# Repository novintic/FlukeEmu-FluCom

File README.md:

# FlukeEmu-FluCom
A HW/SW solution for Fluke 9010 mainframe emulation

The Idea is to use a Raspberry Pi to run a Fluke 9010a emulator in software and interface with the hardware (pods) by means
of an add on board/hat (basically to shift the levels and provide power to the pod). So far we have progressed from a proof
of concept to a pretty solid and stable emulation.

The advantages of using an approach like this are many, amongst them:
* cheap Fluke 9010a mainframe replacement using modern technology and thereby adding stuff like network capability, wireless LAN, remote access/VNC, bluetooth etc ‚for free‘
* the interface board can supply all the power rails to the pod so only one 12V wall adapter is needed to power the RaspberryPi and the pods
* the whole setup is portable and compact, you could in theory put the whole thing inside your cabinet/UUT and comfortably use VNC to remote control the Fluke. You could also run the thing ‚headless‘ making it even smaller.

For further instruction on the fluCom board, please check: FlukeEmu-FluCom/fluCom/readme.md

For further instruction on the flukeEmuWx software, please check: FlukeEmu-FluCom/flukeEmuWx/readme.md

## Credits
We would like to credit Adam Courchesne (@onecircuit) for coming up with the idea of a Fluke emulator and hardware combination
and of course for being the first one to actually write one and make it available.

## See also
https://forums.arcade-museum.com/threads/flukeemu-flucom-fluke-9010a-microsystem-troubleshooter-emulator.503305/

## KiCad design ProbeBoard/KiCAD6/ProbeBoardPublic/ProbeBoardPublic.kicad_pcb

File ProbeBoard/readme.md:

# Probe add-on- board for FluCom Raspberry Pi HAT

This add-on board for the FluCom Raspberry Pi HAT provides full probe functionality for the FlukeEmu/FluCom hardware/software Emulation of the Fluke 9010A Micro-System Troubleshooter.

Basically this makes the Fluke 9010A emulation feature- complete.

As much of the original circuitry as possible was implemented using a Raspberry PICO microcontroller. 

However, due to the original design of the probe, a significant amount of analog circuitry had to be reproduced in order to keep the system working with legacy probes.

The board and its design files are made available under the CERN Open Hardware License: https://ohwr.org/project/cernohl/wikis/Documents/CERN-OHL-version-2

Novitntic 11/2022

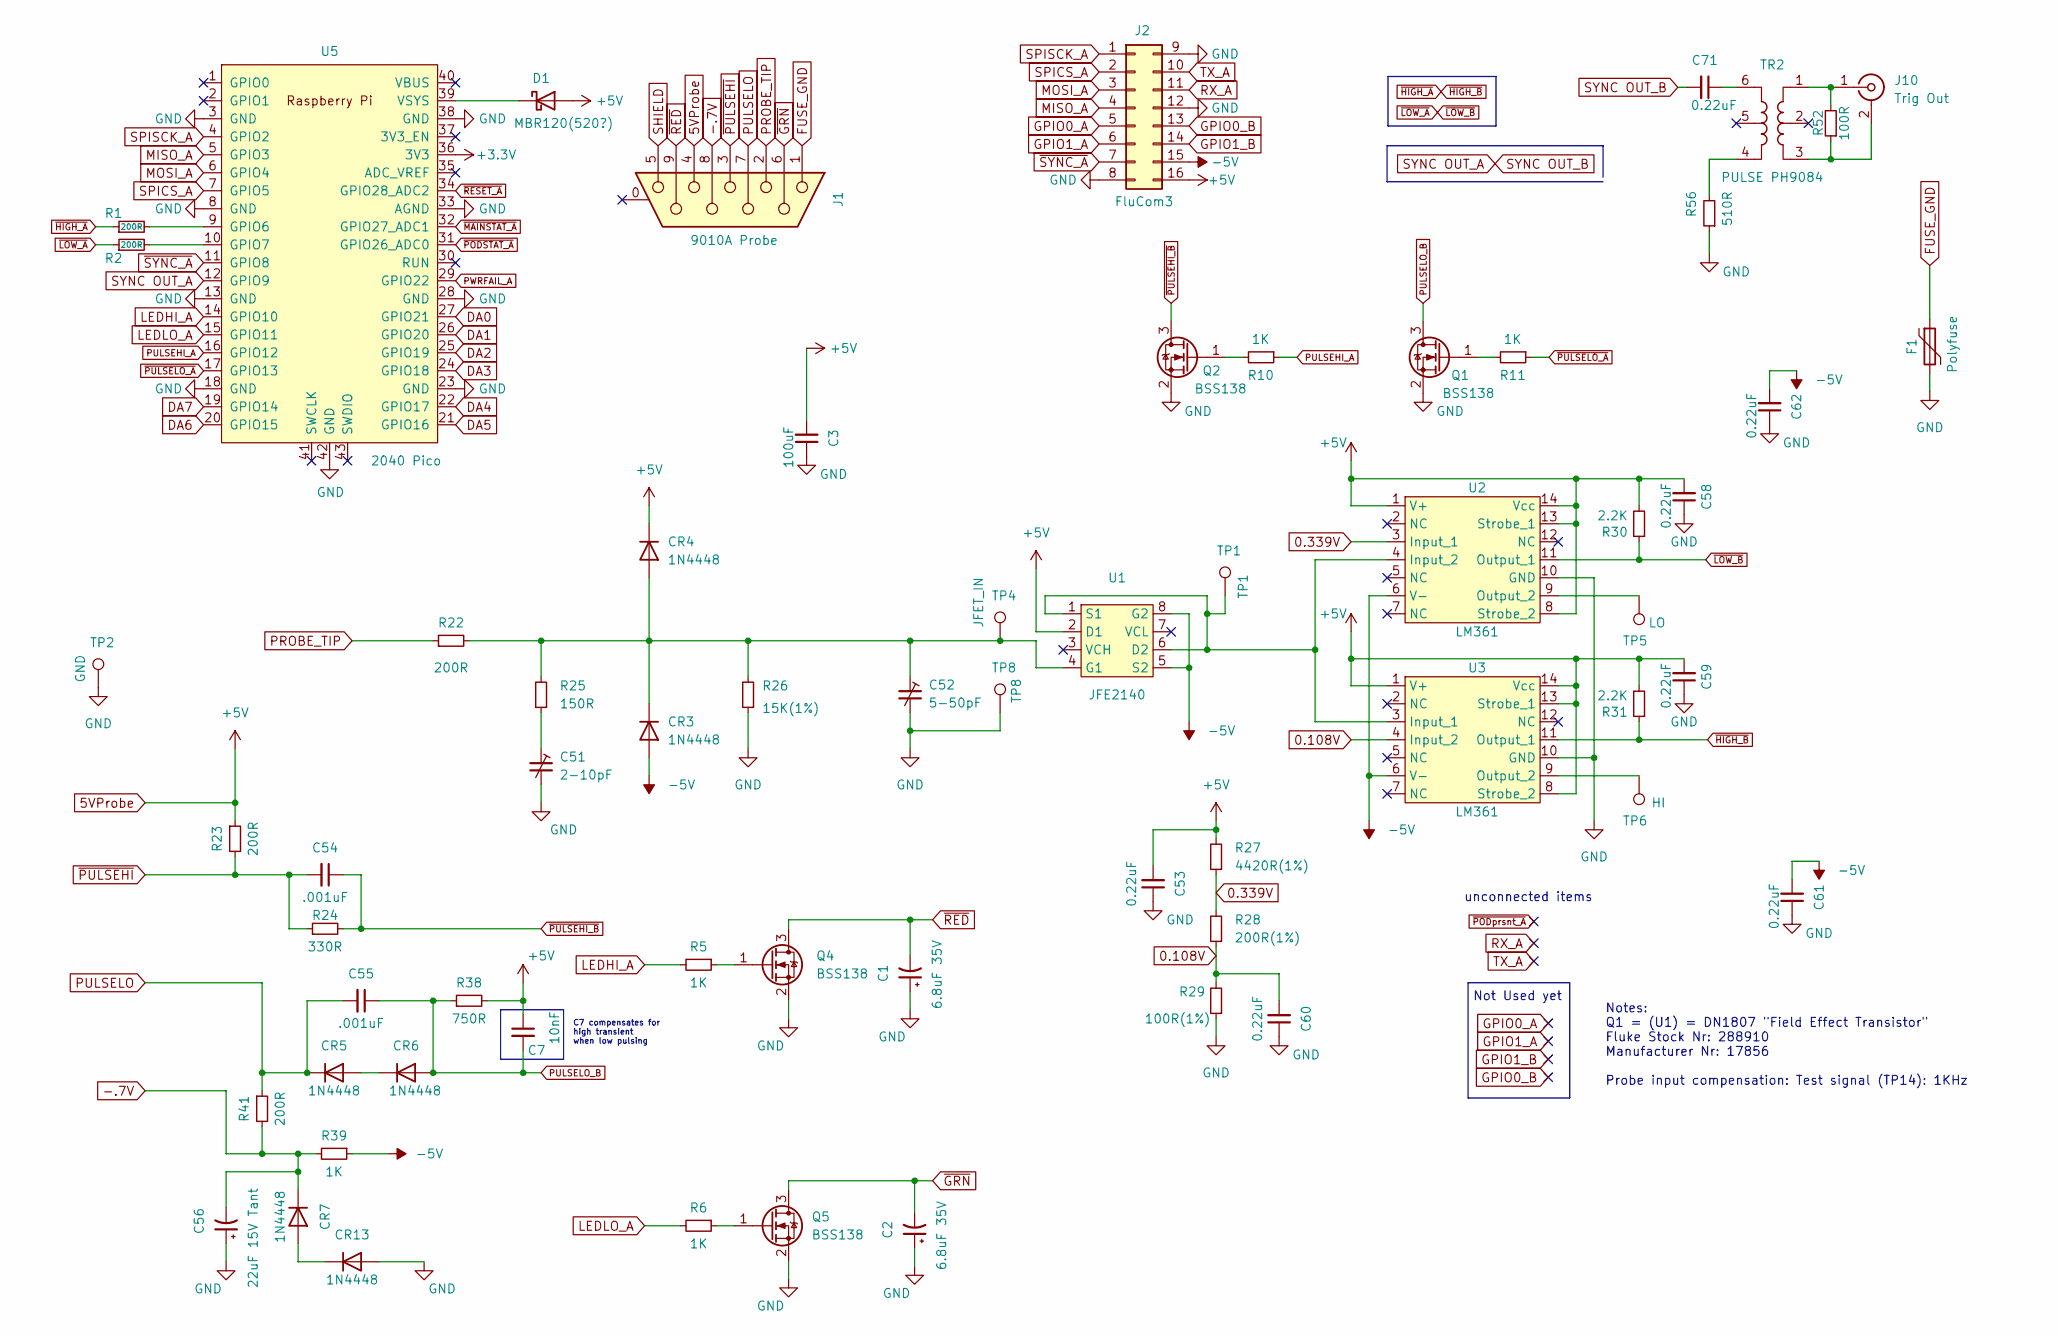
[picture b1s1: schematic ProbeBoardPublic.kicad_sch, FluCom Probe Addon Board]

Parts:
C1, C2: 6.8uF 35V; C_0805_2012Metric_Pad1.18x1.45mm_HandSolder
C3: 100uF; CP_Radial_D5.0mm_P2.50mm
C7: 10nF; C_0805_2012Metric_Pad1.18x1.45mm_HandSolder
C51: 2-10pF; C_1210_3225Metric
C52: 5-50pF; C_1210_3225Metric
C53, C58, C59, C60, C61, C62, C71: 0.22uF; C_0805_2012Metric_Pad1.18x1.45mm_HandSolder
C54, C55: .001uF; C_0805_2012Metric_Pad1.18x1.45mm_HandSolder
C56: 22uF 15V Tant; C_0805_2012Metric_Pad1.18x1.45mm_HandSolder
CR3, CR4, CR5, CR6, CR7, CR13: 1N4448; Nexperia_CFP3_SOD-123W
D1: MBR120(520?); Nexperia_CFP3_SOD-123W
F1: Polyfuse; C_1206_3216Metric_Pad1.33x1.80mm_HandSolder
J1: 9010A Probe; DSUB-9_Female_Horizontal_P2.77x2.84mm_EdgePinOffset4.94mm_H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
J2: FluCom3; PinHeader_2x08_P2.54mm_Vertical
J10: Trig Out; BNC_TEConnectivity_1478035_Horizontal
Q1, Q2, Q4, Q5: BSS138; SOT-23
R1, R2, R22, R23, R41: 200R; R_0805_2012Metric_Pad1.20x1.40mm_HandSolder
R5, R6, R10, R11, R39: 1K; R_0805_2012Metric_Pad1.20x1.40mm_HandSolder
R24: 330R; R_0805_2012Metric_Pad1.20x1.40mm_HandSolder
R25: 150R; R_0805_2012Metric_Pad1.20x1.40mm_HandSolder
R26: 15K(1%); R_0805_2012Metric_Pad1.20x1.40mm_HandSolder
R27: 4420R(1%); R_0805_2012Metric_Pad1.20x1.40mm_HandSolder
R28: 200R(1%); R_0805_2012Metric_Pad1.20x1.40mm_HandSolder
R29: 100R(1%); R_0805_2012Metric_Pad1.20x1.40mm_HandSolder
R30, R31: 2.2K; R_0805_2012Metric_Pad1.20x1.40mm_HandSolder
R38: 750R; R_0805_2012Metric_Pad1.20x1.40mm_HandSolder
R52: 100R; R_0805_2012Metric_Pad1.20x1.40mm_HandSolder
R56: 510R; R_0805_2012Metric_Pad1.20x1.40mm_HandSolder
TP1: TP1; PinHeader_1x01_P2.54mm_Vertical
TP2: GND; PinHeader_1x01_P2.54mm_Vertical
TP4: JFET_IN; PinHeader_1x01_P2.54mm_Vertical
TP5: LO; PinHeader_1x01_P2.54mm_Vertical
TP6: HI; PinHeader_1x01_P2.54mm_Vertical
TP8: TP8; PinHeader_1x01_P2.54mm_Vertical
TR2: PULSE PH9084; Pulse_P0926NL
U1: JFE2140; SOIC-8_3.9x4.9mm_P1.27mm
U2, U3: LM361; SOIC-14_3.9x8.7mm_P1.27mm
U5: 2040 Pico; RPi_Pico_SMD_TH

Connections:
0.108V: C60.2, R28.1, R29.2, U3.4 (Input_2)
0.339V: R27.1, R28.2, U2.3 (Input_1)
5VProbe: C3.2, C7.1, C53.2, C58.2, C59.2, CR4.1 (K), D1.2 (A), J1.4, J2.16, R23.1, R27.2, R30.2, R31.2, R38.2, U1.2 (D1), U2.1 (V+), U2.8 (Strobe_2), U2.13 (Strobe_1), U2.14 (Vcc), U3.1 (V+), U3.8 (Strobe_2), U3.13 (Strobe_1), U3.14 (Vcc)
+3V3: U5.36 (3V3)
-5V: C61.2, C62.2, CR3.2 (A), J2.15, R39.1, U1.5 (S2), U1.8 (G2), U2.6 (V-), U3.6 (V-)
-.7V: C56.2, CR7.1 (K), J1.8, R39.2, R41.2
DA0: U5.27 (GPIO21)
DA1: U5.26 (GPIO20)
DA2: U5.25 (GPIO19)
DA3: U5.24 (GPIO18)
DA4: U5.22 (GPIO17)
DA5: U5.21 (GPIO16)
DA6: U5.20 (GPIO15)
DA7: U5.19 (GPIO14)
FUSE_GND: F1.1, J1.1
GND: C1.1, C2.1, C3.1, C51.2, C52.2, C53.1, C56.1, C58.1, C59.1, C60.1, C61.1, C62.1, CR13.2 (A), F1.2, J2.8, J2.9, J2.12, Q1.2 (S), Q2.2 (S), Q4.2 (S), Q5.2 (S), R26.1, R29.1, R56.1, TP2.1, TP8.1, U2.10 (GND), U3.10 (GND), U5.3 (GND), U5.8 (GND), U5.13 (GND), U5.18 (GND), U5.23 (GND), U5.28 (GND), U5.33 (AGND), U5.38 (GND), U5.42 (GND)
GPIO0_A: J2.5
GPIO0_B: J2.13
GPIO1_A: J2.6
GPIO1_B: J2.14
LEDHI_A: R5.2, U5.14 (GPIO10)
LEDLO_A: R6.2, U5.15 (GPIO11)
MISO_A: J2.4, U5.5 (GPIO3)
MOSI_A: J2.3, U5.6 (GPIO4)
unnamed: C51.1, R25.1
unnamed: C52.1, CR3.1 (K), CR4.2 (A), R22.2, R25.2, R26.2, TP4.1, U1.4 (G1)
unnamed: C71.1, TR2.6
unnamed: CR5.2 (A), CR6.1 (K)
unnamed: CR7.2 (A), CR13.1 (K)
unnamed: D1.1 (K), U5.39 (VSYS)
unnamed: J10.1 (In), R52.2, TR2.1
unnamed: J10.2 (Ext), R52.1, TR2.3
unnamed: Q1.1 (G), R11.2
unnamed: Q2.1 (G), R10.2
unnamed: Q4.1 (G), R5.1
unnamed: Q5.1 (G), R6.1
unnamed: R1.2, U5.9 (GPIO6)
unnamed: R2.2, U5.10 (GPIO7)
unnamed: R56.2, TR2.4
unnamed: TP1.1, U1.1 (S1), U1.6 (D2), U2.4 (Input_2), U3.3 (Input_1)
unnamed: TP5.1, U2.9 (Output_2)
unnamed: TP6.1, U3.9 (Output_2)
PROBE_TIP: J1.2, R22.1
PULSEHI_A: R10.1, U5.16 (GPIO12)
PULSELO: C55.2, CR5.1 (K), J1.7, R41.1
PULSELO_B: C7.2, C55.1, CR6.2 (A), Q1.3 (D), R38.1
PWRFAIL_A: U5.29 (GPIO22)
RX_A: J2.11
SHIELD: J1.5
SPICS_A: J2.2, U5.7 (GPIO5)
SPISCK_A: J2.1, U5.4 (GPIO2)
SYNC OUT_A: C71.2, U5.12 (GPIO9)
TX_A: J2.10
~GRN: C2.2, J1.6, Q5.3 (D)
~HIGH_A: R1.1, R31.1, U3.11 (Output_1)
~LOW_A: R2.1, R30.1, U2.11 (Output_1)
~MAINSTAT_A: U5.32 (GPIO27_ADC1)
~PODSTAT_A: U5.31 (GPIO26_ADC0)
~PULSEHI_B: C54.1, Q2.3 (D), R24.2
~PULSEHI: C54.2, J1.3, R23.2, R24.1
~PULSELO_A: R11.1, U5.17 (GPIO13)
~RED: C1.2, J1.9, Q4.3 (D)
~RESET_A: U5.34 (GPIO28_ADC2)
~SYNC_A: J2.7, U5.11 (GPIO8)

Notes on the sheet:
C7 compensates for high transient when low pulsing
unconnected items
Notes: Q1 = (U1) = DN1807 "Field Effect Transistor" Fluke Stock Nr: 288910 Manufacturer Nr: 17856 Probe input compensation: Test signal (TP14): 1KHz
Not Used yet

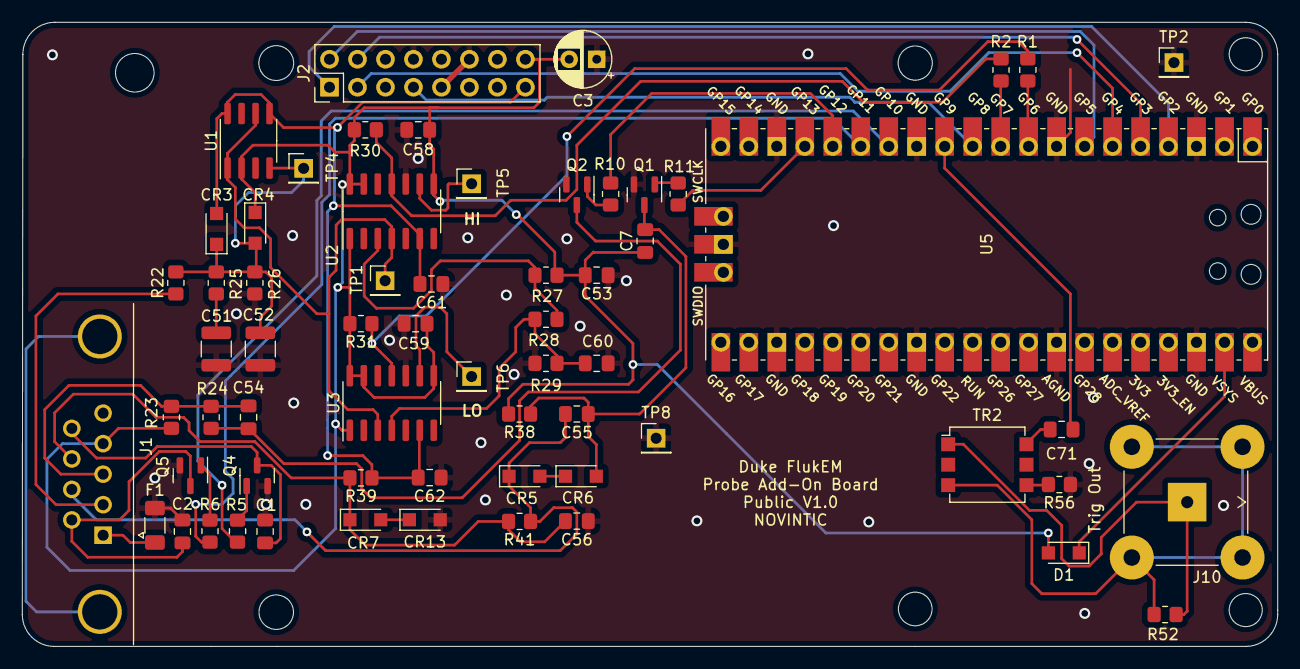
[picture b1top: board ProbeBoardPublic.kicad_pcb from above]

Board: 2 copper layers, 114.0 x 56.6 mm, 63 parts (0 on the bottom side), 44 nets.

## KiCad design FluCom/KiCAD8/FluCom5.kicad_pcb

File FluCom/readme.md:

# FluCom
The FluCom Interface is a stack-on board (HAT) for a Raspberry Pi 3 or higher. It’s purpose is to interface with Pods for the Fluke 9000 series Microsystem Troubleshooter which is still used today to diagnose and repair vintage computer equipment such as arcade game pcbs.

It is designed to be used in conjunction with the FlukeEmu software.

The idea behind the project is to use readily available parts to provide an as-simple-as-possible (cheap) way to replace a Fluke 9010a Mainframe.

The board and its design files are made available under the CERN Open Hardware License: https://ohwr.org/project/cernohl/wikis/Documents/CERN-OHL-version-2

Novitntic 03/2022

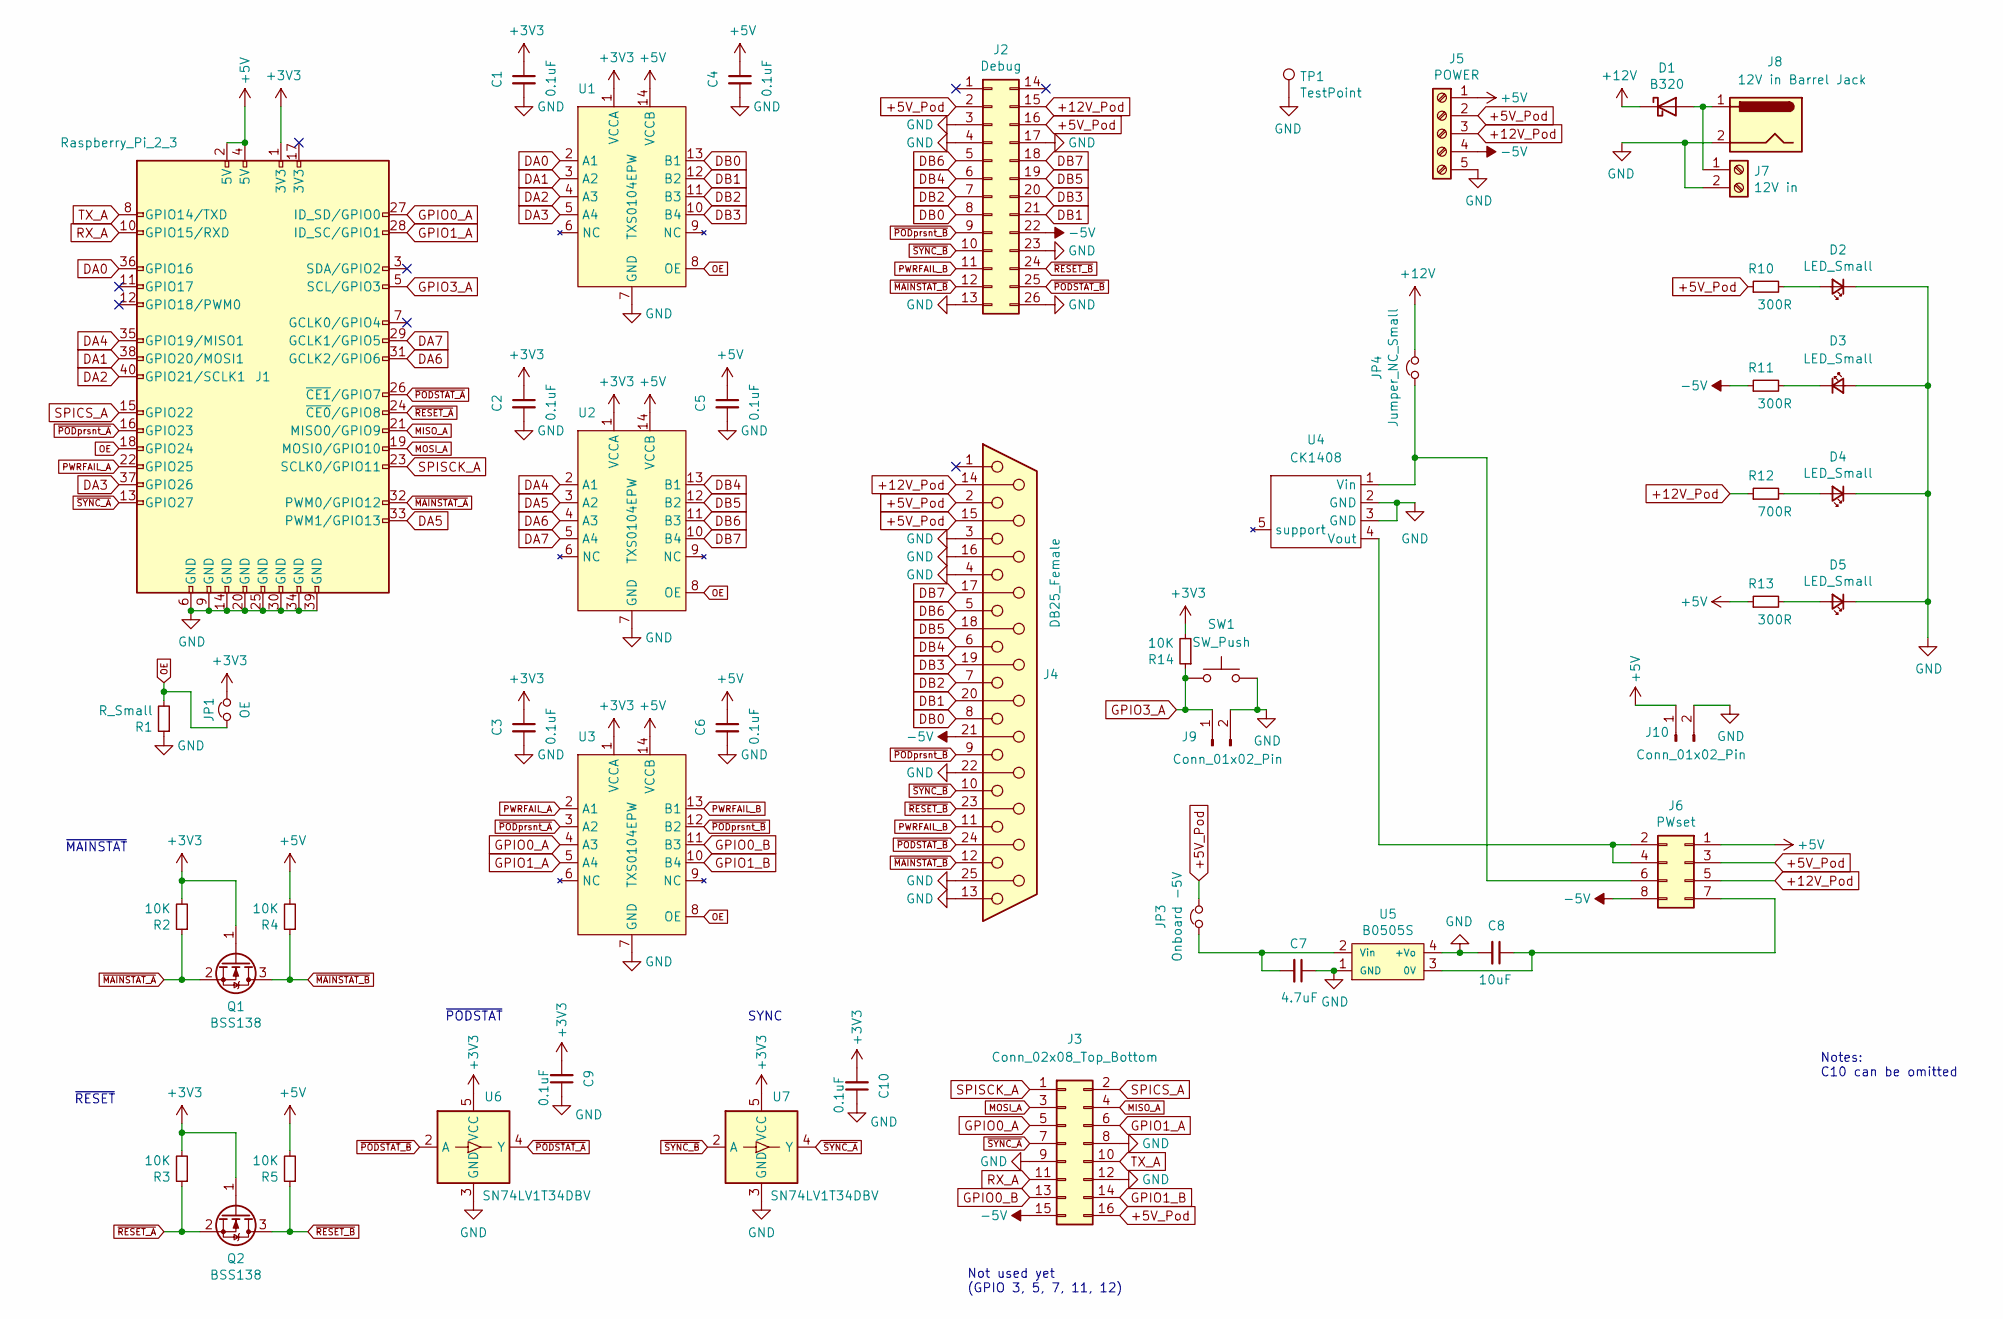
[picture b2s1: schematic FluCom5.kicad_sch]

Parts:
C1, C2, C3, C4, C5, C6: 0.1uF; C_0805_2012Metric_Pad1.18x1.45mm_HandSolder; LCSC C138340
C7: 4.7uF; C_0805_2012Metric_Pad1.18x1.45mm_HandSolder; LCSC C77077
C8: 10uF; C_0805_2012Metric_Pad1.18x1.45mm_HandSolder; LCSC C83061
C9, C10: 0.1uF; C_0805_2012Metric_Pad1.18x1.45mm_HandSolder; LCSC C126469
D1: B320; D_SMC; LCSC C134448
D2, D3, D4, D5: LED_Small; LED_0805_2012Metric_Pad1.15x1.40mm_HandSolder; LCSC C189307
J1: Raspberry_Pi_2_3; PinHeader_2x20_P2.54mm_Vertical
J2: Debug; PinHeader_2x13_P2.54mm_Vertical_Fluke_Numbering_mirrored
J3: Conn_02x08_Top_Bottom; PinHeader_2x08_P2.54mm_Vertical
J4: DB25_Female; DSUB-25_Female_Horizontal_P2.77x2.54mm_EdgePinOffset9.40mm
J5: POWER; TerminalBlock_bornier-5_P5.08mm
J6: PWset; PinHeader_2x04_P2.54mm_Vertical
J7: 12V in; TerminalBlock_bornier-2_P5.08mm
J8: 12V in Barrel Jack; BarrelJack_Horizontal
J9, J10: Conn_01x02_Pin; PinHeader_1x02_P2.54mm_Vertical
JP1: OE; PinHeader_1x02_P2.54mm_Vertical
JP3: Onboard -5V; PinHeader_1x02_P2.54mm_Vertical
JP4: Jumper_NC_Small; PinHeader_1x02_P2.54mm_Vertical
Q1, Q2: BSS138; SOT-23; LCSC C5190146
R1: R_Small; R_0805_2012Metric_Pad1.20x1.40mm_HandSolder; LCSC C510098
R2, R3, R4, R5, R14: 10K; R_0805_2012Metric_Pad1.20x1.40mm_HandSolder; LCSC C510098
R10, R11, R13: 300R; R_0805_2012Metric_Pad1.20x1.40mm_HandSolder; LCSC C365284
R12: 700R; R_0805_2012Metric_Pad1.20x1.40mm_HandSolder; LCSC C229239
SW1: SW_Push; SW_Push_1P1T_NO_CK_KSC6xxJ
TP1: TestPoint; PinHeader_1x01_P2.54mm_Vertical
U1, U2, U3: TXS0104EPW; SOIC-14_3.9x8.7mm_P1.27mm; LCSC C79342
U4: CK1408
U5: B0505S; Converter_DCDC_muRata_CRE1xxxxxxSC_THT
U6, U7: SN74LV1T34DBV; SOT-23-5; LCSC C100024

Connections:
+3V3: C1.1, C2.1, C3.1, C9.2, C10.2, J1.1 (3V3), JP1.2, Q1.1 (G), Q2.1 (G), R2.2, R3.2, R14.2, U1.1 (VCCA), U2.1 (VCCA), U3.1 (VCCA), U6.5 (VCC), U7.5 (VCC)
+5V: C4.1, C5.1, C6.1, J1.2 (5V), J1.4 (5V), J5.1, J6.1, J10.1, R4.2, R5.2, R13.1, U1.14 (VCCB), U2.14 (VCCB), U3.14 (VCCB)
+5V_Pod: J2.2, J2.16, J3.16, J4.2, J4.15, J5.2, J6.3, JP3.2, R10.1
+12V: D1.1 (K), JP4.2
+12V_Pod: J2.15, J4.14, J5.3, J6.5, R12.1
-5V: J2.22, J3.15, J4.21, J5.4, J6.8, R11.1
DA0: J1.36 (GPIO16), U1.2 (A1)
DA1: J1.38 (GPIO20/MOSI1), U1.3 (A2)
DA2: J1.40 (GPIO21/SCLK1), U1.4 (A3)
DA3: J1.37 (GPIO26), U1.5 (A4)
DA4: J1.35 (GPIO19/MISO1), U2.2 (A1)
DA5: J1.33 (PWM1/GPIO13), U2.3 (A2)
DA6: J1.31 (GCLK2/GPIO6), U2.4 (A3)
DA7: J1.29 (GCLK1/GPIO5), U2.5 (A4)
DB0: J2.8, J4.8, U1.13 (B1)
DB1: J2.21, J4.20, U1.12 (B2)
DB2: J2.7, J4.7, U1.11 (B3)
DB3: J2.20, J4.19, U1.10 (B4)
DB4: J2.6, J4.6, U2.13 (B1)
DB5: J2.19, J4.18, U2.12 (B2)
DB6: J2.5, J4.5, U2.11 (B3)
DB7: J2.18, J4.17, U2.10 (B4)
GND: C1.2, C2.2, C3.2, C4.2, C5.2, C6.2, C7.1, C8.2, C9.1, C10.1, D2.1 (K), D3.2 (A), D4.1 (K), D5.1 (K), J1.6 (GND), J1.9 (GND), J1.14 (GND), J1.20 (GND), J1.25 (GND), J1.30 (GND), J1.34 (GND), J1.39 (GND), J2.3, J2.4, J2.13, J2.17, J2.23, J2.26, J3.8, J3.9, J3.12, J4.3, J4.4, J4.13, J4.16, J4.22, J4.25, J5.5, J7.2, J8.2, J9.2, J10.2, R1.1, SW1.2, TP1.1, U1.7 (GND), U2.7 (GND), U3.7 (GND), U4.2 (GND), U4.3 (GND), U5.1 (GND), U5.4 (+Vo), U6.3 (GND), U7.3 (GND)
GPIO0_A: J1.27 (ID_SD/GPIO0), J3.5, U3.4 (A3)
GPIO0_B: J3.13, U3.11 (B3)
GPIO1_A: J1.28 (ID_SC/GPIO1), J3.6, U3.5 (A4)
GPIO1_B: J3.14, U3.10 (B4)
GPIO3_A: J1.5 (SCL/GPIO3), J9.1, R14.1, SW1.1
MISO_A: J1.21 (MISO0/GPIO9), J3.4
MOSI_A: J1.19 (MOSI0/GPIO10), J3.3
unnamed: D1.2 (A), J7.1, J8.1
unnamed: D2.2 (A), R10.2
unnamed: D3.1 (K), R11.2
unnamed: D4.2 (A), R12.2
unnamed: D5.2 (A), R13.2
unnamed: J6.2, J6.4, U4.4 (Vout)
unnamed: J6.6, JP4.1, U4.1 (Vin)
unnamed: C8.1, J6.7, U5.3 (0V)
unnamed: C7.2, JP3.1, U5.2 (Vin)
OE: J1.18 (GPIO24), JP1.1, R1.2, U1.8 (OE), U2.8 (OE), U3.8 (OE)
PWRFAIL_A: J1.22 (GPIO25), U3.2 (A1)
PWRFAIL_B: J2.11, J4.11, U3.13 (B1)
RX_A: J1.10 (GPIO15/RXD), J3.11
SPICS_A: J1.15 (GPIO22), J3.2
SPISCK_A: J1.23 (SCLK0/GPIO11), J3.1
TX_A: J1.8 (GPIO14/TXD), J3.10
~MAINSTAT_A: J1.32 (PWM0/GPIO12), Q1.2 (S), R2.1
~MAINSTAT_B: J2.12, J4.12, Q1.3 (D), R4.1
~PODSTAT_A: J1.26 (~CE1/GPIO7), U6.4 (Y)
~PODSTAT_B: J2.25, J4.24, U6.2 (A)
~PODprsnt_A: J1.16 (GPIO23), U3.3 (A2)
~PODprsnt_B: J2.9, J4.9, U3.12 (B2)
~RESET_A: J1.24 (~CE0/GPIO8), Q2.2 (S), R3.1
~RESET_B: J2.24, J4.23, Q2.3 (D), R5.1
~SYNC_A: J1.13 (GPIO27), J3.7, U7.4 (Y)
~SYNC_B: J2.10, J4.10, U7.2 (A)

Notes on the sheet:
SYNC
~{PODSTAT}
~{RESET}
~{MAINSTAT}
Notes: C10 can be omitted
Not used yet (GPIO 3, 5, 7, 11, 12)

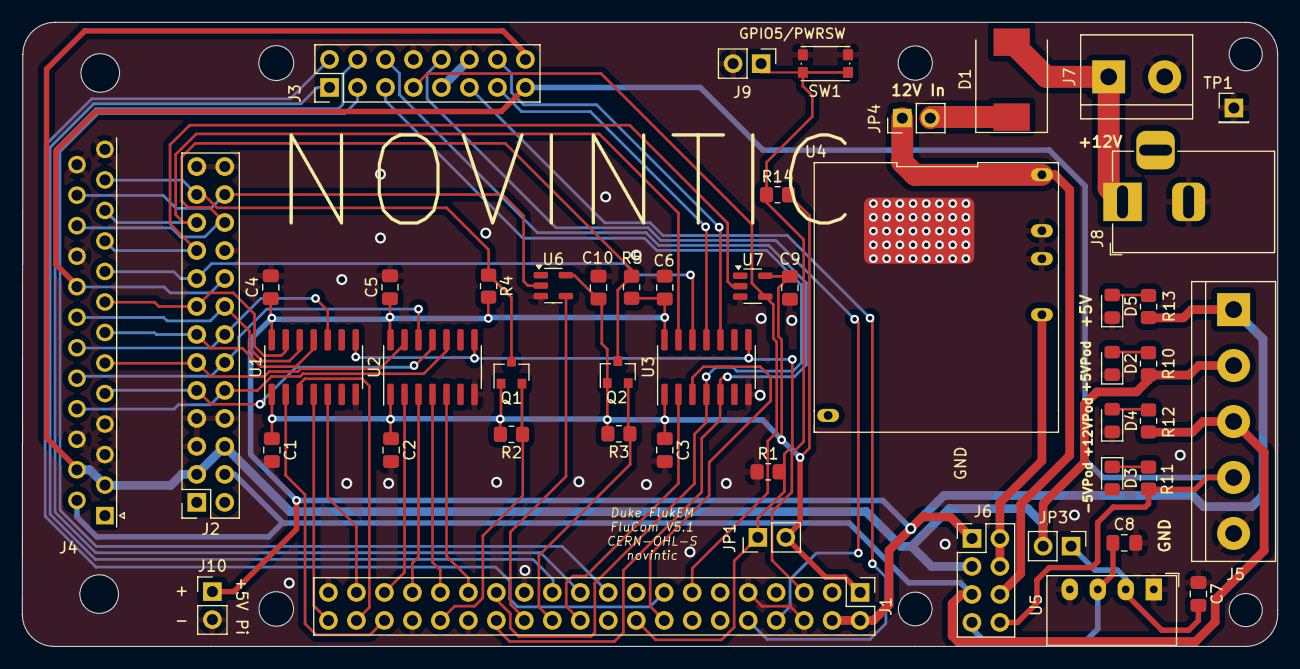
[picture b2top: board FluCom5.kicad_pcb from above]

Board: 2 copper layers, 114.0 x 56.7 mm, 49 parts (0 on the bottom side), 56 nets.

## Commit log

2022-04-09 Initial upload
2022-04-09 Do not track
2022-04-09 Rename readme.txt to readme.md
2022-04-09 Added readme paths
2022-04-09 added define for Z80
2022-04-09 Disable wxSound
2022-04-09 Project file clean-up. Only RPI now
2022-04-09 'old' keyclick
2022-04-11 reformatted
2022-04-18 Add files via upload
    Added DigiKey parts numbers
2022-04-18 Added DigiKey parts numbers
2022-05-07 Serial file support
2022-05-13 Fixed crash when sending file. Added messages when media folder is not found
2022-05-13 Update readme.md
    Added run instructions
2022-05-13 Update readme.md
    typo
2022-05-13 Create manual.md
    A first attempt a sort of manual
2022-05-14 Update manual.md
    typos!!!
2022-05-14 Update manual.md
    update
2022-06-09 Parse command line to allow starting fullscreen
2022-06-14 readme.md: remove intructions on installing old Z80 emulator
2022-06-14 z80_source_code.txt: updated with info about new Z80 code
2022-06-14 Added free Z80 emulator source
2022-06-14 Fix interface between FlukeEmuHw and new Z80 emulator API
2022-06-14 FlukeEmuWx.cbp: switch to files in new Z80 emulator
2022-06-17 Update FlukeEmuWxMain.cpp
    new version
2022-06-20 Fix Window title
2022-07-16 new probeboard class
2022-07-16 1st probeboard integration
2022-07-25 Added FluCom3
    This version of the interface board is needed to add the probe board. The only changes are the new pin header for this purpose. The older versions will still work fine. So far, there is only a SOIC v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
2022-07-25 Update readme - versions.txt
    Added FluCom3
2022-07-25 Updated for FluCom3 Schematics
2022-07-28 moved FluCom2 files to 'obsolete' folder
2022-08-19 Master (#8)
    * new probeboard class
    * Update readme.md
    Added run instructions
    * Update readme.md
    typo
    * Create manual.md
2022-08-19 Delete FlukeEmuWx.depend
    Not needed
2022-08-20 fix level display
2022-08-20 updated gitignore
2022-08-20 fixed mode set output
2022-08-30 fixed probe com
2022-09-06 fixed wrong hi lo byte in signature
2022-09-06 fix sync signal
2022-11-25 Delete Build Manual and BOM.pdf
    Replaced file with new version and new name
2022-11-25 Add files via upload
    New version of manual (includes changes necessary for using the probe add-on board) and new filename.
2022-11-25 First public release of probe board.
2022-12-09 Added first release of firmware
2023-01-01 Changed J3 in schematic to alternate numbering
    Changed J3 in schematic to alternate numbering to make it consistent with the physical footprint used on the board
2023-01-01 Changed numbering of J3 in build manual schematic
    Changed J3 in build manual's schematic to alternate numbering to make it consistent with the physical footprint used on the board
2023-04-16 Add files via upload
    Increased track with of +5V POD rail (should be able to provide up to 2A for larger pods like 68K)
2023-04-16 Add files via upload
    Increased track width of +5V POD rail (should be able to provide up to 2A for larger pods like 68K)
2024-04-23 hi-low keys fixed, added numlock enter, key display on alt, probe LEDS
2024-04-23 Layout and render optimizations
2024-04-27 Probe sounds using wxsound and SDL, alpha keys, emu settings menu key
2024-05-09 Add files via upload
    Uploaded ProbeBoard Public V5
2024-05-09 Add files via upload
    Uploaded FluCom V5
2024-05-19 Update readme.txt
    About the fuse F1
2024-10-06 Add files via upload
    Removed 40 Pin connector vom Gerbers and production files to avoid confusion
2024-12-05 Add files via upload
    Added notes about 'larger' PODs and power supply
2025-01-12 sound enable/disable
2025-01-12 probe sound off by default
2025-01-12 Pull main changes to devmain (#9)
    * Delete Build Manual and BOM.pdf
    Replaced file with new version and new name
    * Add files via upload
    New version of manual (includes changes necessary for using the probe add-on board) and new filename.
    * First public release of probe board.
    * Delete Probe Board Build Manual and BOM.pdf
2025-01-12 Revert "Pull main changes to devmain (#9)"
    This reverts commit b06e7216cb19aedc7d3f1abd690329d858e026d4.
2025-01-15 fixed wrong pointer comparison, proper shutdown, added sound type debug
2025-01-15 first version of build script and deb script
2025-01-19 added comments to script
2025-01-19 readme updated
2025-02-16 User emu speed cli switch, probeboard detetcion, probe LED upgrade, memory leak fix
2025-02-16 fixed samplerate
2025-02-16 version 0.97b

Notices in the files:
FluCom/KiCAD8/FluCom5.kicad_pcb:
CERN-OHL-S
